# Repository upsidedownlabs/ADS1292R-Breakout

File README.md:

# Upside Down Labs ADS1292R

Upside Down Lab's ADS1292R breakout board for 2ch ECG + 1ch Respiration.

## v0.2 Board

## License
#### Hardware
CERN Open Hardware License Version 2 - Strongly Reciprocal ([CERN-OHL-S-2.0](https://spdx.org/licenses/CERN-OHL-S-2.0.html)).

#### Software
MIT open source [license](http://opensource.org/licenses/MIT).

#### Documentation:
<br />This work is licensed under a <a rel="license" href="http://creativecommons.org/licenses/by/4.0/">Creative Commons Attribution 4.0 International License</a>.

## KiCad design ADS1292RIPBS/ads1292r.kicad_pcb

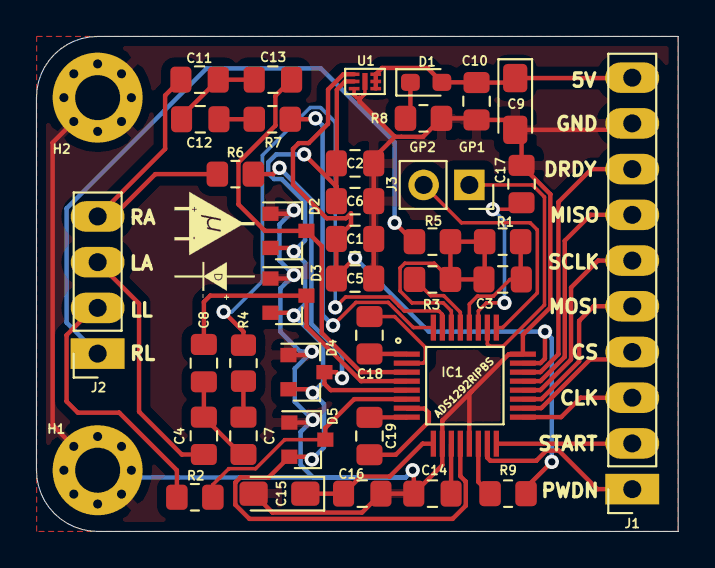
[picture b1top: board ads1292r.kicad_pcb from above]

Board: 2 copper layers, 35.7 x 27.5 mm, 40 parts (0 on the bottom side), 40 nets.

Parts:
C1, C2, C14, C17: 2.2uF; C_0805_2012Metric_Pad1.18x1.45mm_HandSolder
C3: 1.5nF; C_0805_2012Metric_Pad1.18x1.45mm_HandSolder
C4, C5, C6, C10, C11, C16: 100nF; C_0805_2012Metric_Pad1.18x1.45mm_HandSolder
C7, C8, C12, C13: 2.2nF; C_0805_2012Metric_Pad1.18x1.45mm_HandSolder
C9, C15: 22uF; CP_EIA-3216-18_Kemet-A_Pad1.58x1.35mm_HandSolder
C18, C19: 4.7nF; C_0805_2012Metric_Pad1.18x1.45mm_HandSolder
D1: LED; LED_0603_1608Metric_Pad1.05x0.95mm_HandSolder
D2, D3, D4, D5: BAV99; SOT-23
H1, H2: MountingHole_Pad; MountingHole_2.5mm_Pad_Via
IC1: ADS1292RIPBS
J1: Conn_01x10_Male; PinSocket_1x10_P2.54mm_Vertical
J2: Conn_01x04_Male; PinSocket_1x04_P2.54mm_Vertical
J3: Conn_01x02_Male; PinSocket_1x02_P2.54mm_Vertical
R1: 1M; R_0805_2012Metric_Pad1.20x1.40mm_HandSolder
R2, R6: 51K; R_0805_2012Metric_Pad1.20x1.40mm_HandSolder
R3, R5: 100K; R_0805_2012Metric_Pad1.20x1.40mm_HandSolder
R4, R7: 40K; R_0805_2012Metric_Pad1.20x1.40mm_HandSolder
R8: 1K; R_0805_2012Metric_Pad1.20x1.40mm_HandSolder
R9: 10K; R_0805_2012Metric_Pad1.20x1.40mm_HandSolder
U1: TLV7163318PDPQR; S-PX2SON-N6

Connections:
5V: C9.1, C10.1, D1.2, J1.10, U1.4, U1.5, U1.6
AVDD: C2.1, C6.1, D2.2, D3.2, D4.2, D5.2, IC1.12, U1.2
CLK: IC1.17, J1.3
CLKSEL: IC1.14, R9.2
CS: IC1.18, J1.4
DIN: IC1.19, J1.5
DOUT: IC1.21, J1.7
DRDY: IC1.22, J1.8
DVDD: C1.1, C5.1, IC1.23, R9.1, U1.1
GND: C1.2, C2.2, C5.2, C6.2, C9.2, C10.2, C14.2, C15.2, C16.2, C17.2, D2.1, D3.1, D4.1, D5.1, H1.1, H2.1, IC1.10, IC1.13, IC1.24, J1.9, R8.2, U1.3, U1.7
GPIO1: IC1.26, J3.1
GPIO2: IC1.25, J3.2
IN1N: C13.1, D2.3, IC1.3
IN1P: C8.1, D3.3, IC1.4
IN2N: D4.3, IC1.5, R6.2
IN2P: D5.3, IC1.6, R2.2
IN3N: IC1.32, R7.1
IN3P: IC1.31, R4.1
LA: C4.1, J2.3
LL: J2.2, R2.1
unnamed: C4.2, C7.1, C8.2
unnamed: C7.2, R4.2
unnamed: C11.2, C12.1, C13.2
unnamed: C12.2, R7.2
unnamed: C18.1, IC1.1
unnamed: C18.2, IC1.2
unnamed: C19.1, IC1.7
unnamed: C19.2, IC1.8
unnamed: D1.1, R8.1
PWDN: IC1.15, J1.1
RA: C11.1, J2.4, R6.1
RL: J2.1, R5.1
RLDIN: IC1.29, R3.2
RLDINV: C3.1, IC1.28, R1.1
RLDOUT: C3.2, IC1.30, R1.2, R3.1, R5.2
SCLK: IC1.20, J1.6
START: IC1.16, J1.2
VCAP1: C14.1, IC1.11
VCAP2: C17.1, IC1.27
VREFP: C15.1, C16.1, IC1.9

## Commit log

2020-12-30 ADS1292RIPBS v0.1
2020-12-31 Update License
2020-12-31 v0.2
2020-12-31 Add v0.2 shematic PDF
2020-12-31 add torso imgae
2020-12-31 add v0.2 dimensions image
2020-12-31 add v0.2 schematic image
2020-12-31 add v0.2 back image
2020-12-31 add v0.2 front image
2020-12-31 update PCB
